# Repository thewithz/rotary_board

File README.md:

# rotary_board
A custom 65% keyboard design featuring 4 rotary encoders in place of the pg up, pg down, home, and end keys

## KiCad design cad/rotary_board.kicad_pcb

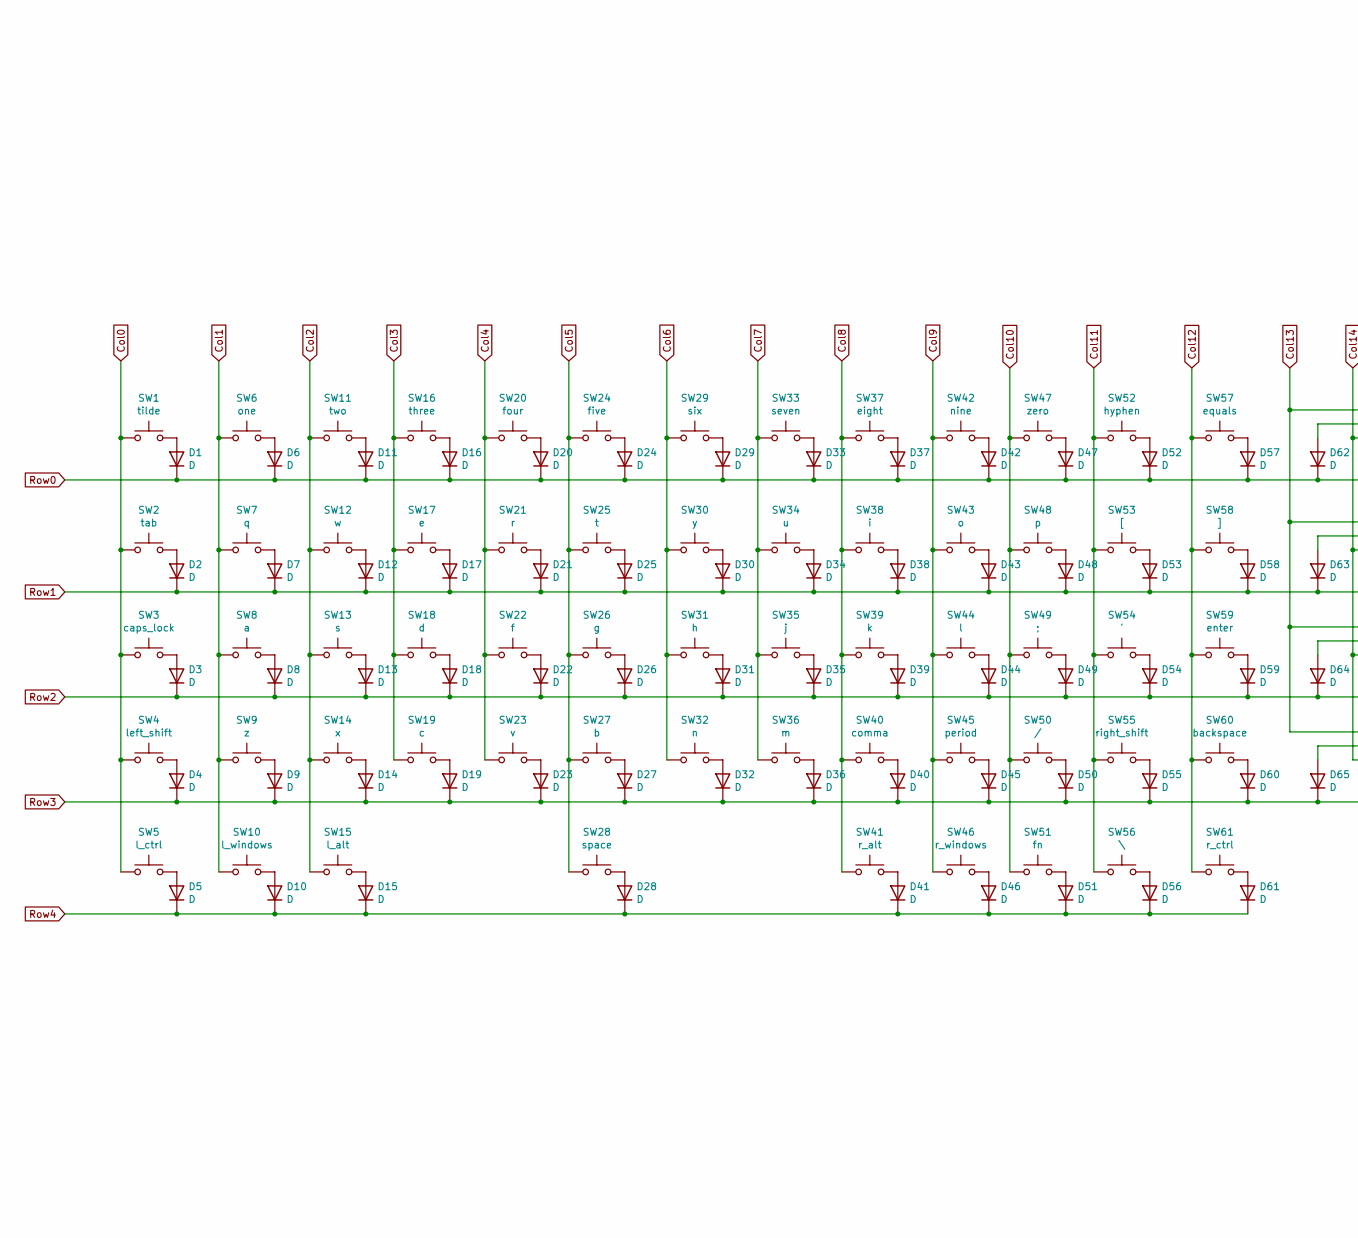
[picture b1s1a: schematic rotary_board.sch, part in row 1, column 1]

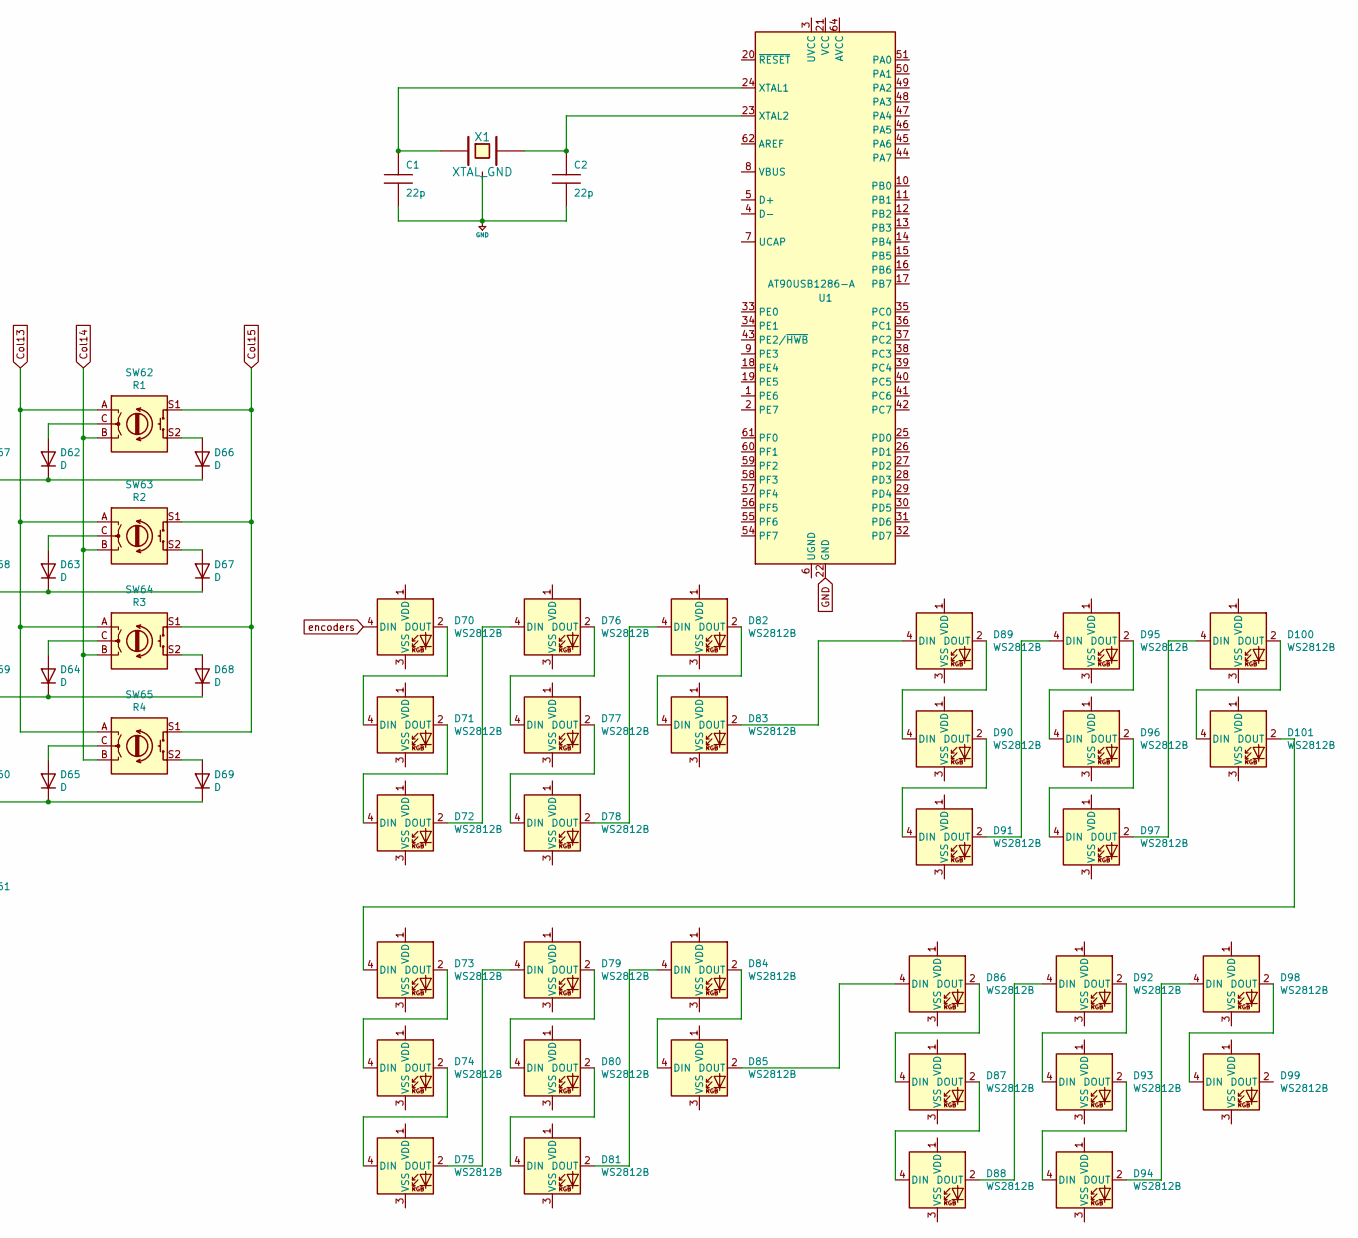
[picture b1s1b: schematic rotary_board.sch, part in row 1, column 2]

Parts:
C1, C2: 22p; CP_Elec_3x5.3
D1, D2, D3, D4, D5, D6, D7, D8, D9, D10, D11, D12, D13, D14, D15, D16, D17, D18, D19, D20, D21, D22, D23, D24, D25, D26, D27, D28, D29, D30, D31, D32, D33, D34, D35, D36, D37, D38, D39, D40, D41, D42, D43, D44, D45, D46, D47, D48, D49, D50, D51, D52, D53, D54, D55, D56, D57, D58, D59, D60, D61, D62, D63, D64, D65, D66, D67, D68, D69: D; D_SOD-123
D70, D71, D72, D73, D74, D75, D76, D77, D78, D79, D80, D81, D82, D83, D84, D85, D86, D87, D88, D89, D90, D91, D92, D93, D94, D95, D96, D97, D98, D99, D100, D101: WS2812B; LED_WS2812B_PLCC4_5.0x5.0mm_P3.2mm
SW1: tilde; SW_Cherry_MX_1.00u_PCB
SW2: tab; SW_Cherry_MX_1.50u_PCB
SW3: caps_lock; SW_Cherry_MX_1.75u_PCB
SW4: left_shift; SW_Cherry_MX_2.25u_PCB
SW5: l_ctrl; SW_Cherry_MX_1.25u_PCB
SW6: one; SW_Cherry_MX_1.00u_PCB
SW7: q; SW_Cherry_MX_1.00u_PCB
SW8: a; SW_Cherry_MX_1.00u_PCB
SW9: z; SW_Cherry_MX_1.00u_PCB
SW10: l_windows; SW_Cherry_MX_1.25u_PCB
SW11: two; SW_Cherry_MX_1.00u_PCB
SW12: w; SW_Cherry_MX_1.00u_PCB
SW13: s; SW_Cherry_MX_1.00u_PCB
SW14: x; SW_Cherry_MX_1.00u_PCB
SW15: l_alt; SW_Cherry_MX_1.25u_PCB
SW16: three; SW_Cherry_MX_1.00u_PCB
SW17: e; SW_Cherry_MX_1.00u_PCB
SW18: d; SW_Cherry_MX_1.00u_PCB
SW19: c; SW_Cherry_MX_1.00u_PCB
SW20: four; SW_Cherry_MX_1.00u_PCB
SW21: r; SW_Cherry_MX_1.00u_PCB
SW22: f; SW_Cherry_MX_1.00u_PCB
SW23: v; SW_Cherry_MX_1.00u_PCB
SW24: five; SW_Cherry_MX_1.00u_PCB
SW25: t; SW_Cherry_MX_1.00u_PCB
SW26: g; SW_Cherry_MX_1.00u_PCB
SW27: b; SW_Cherry_MX_1.00u_PCB
SW28: space; SW_Cherry_MX_6.25u_PCB
SW29: six; SW_Cherry_MX_1.00u_PCB
SW30: y; SW_Cherry_MX_1.00u_PCB
SW31: h; SW_Cherry_MX_1.00u_PCB
SW32: n; SW_Cherry_MX_1.00u_PCB
SW33: seven; SW_Cherry_MX_1.00u_PCB
SW34: u; SW_Cherry_MX_1.00u_PCB
SW35: j; SW_Cherry_MX_1.00u_PCB
SW36: m; SW_Cherry_MX_1.00u_PCB
SW37: eight; SW_Cherry_MX_1.00u_PCB
SW38: i; SW_Cherry_MX_1.00u_PCB
SW39: k; SW_Cherry_MX_1.00u_PCB
SW40: comma; SW_Cherry_MX_1.00u_PCB
SW41: r_alt; SW_Cherry_MX_1.25u_PCB
SW42: nine; SW_Cherry_MX_1.00u_PCB
SW43: o; SW_Cherry_MX_1.00u_PCB
SW44: l; SW_Cherry_MX_1.00u_PCB
SW45: period; SW_Cherry_MX_1.00u_PCB
SW46: r_windows; SW_Cherry_MX_1.25u_PCB
SW47: zero; SW_Cherry_MX_1.00u_PCB
SW48: p; SW_Cherry_MX_1.00u_PCB
SW49: ;; SW_Cherry_MX_1.00u_PCB
SW50: /; SW_Cherry_MX_1.00u_PCB
SW51: fn; SW_Cherry_MX_1.25u_PCB
SW52: hyphen; SW_Cherry_MX_1.00u_PCB
SW53: [; SW_Cherry_MX_1.00u_PCB
SW54: '; SW_Cherry_MX_1.00u_PCB
SW55: right_shift; SW_Cherry_MX_2.75u_PCB
SW56: \\; SW_Cherry_MX_1.50u_PCB
SW57: equals; SW_Cherry_MX_1.00u_PCB
SW58: ]; SW_Cherry_MX_1.00u_PCB
SW59: enter; SW_Cherry_MX_2.25u_PCB
SW60: backspace; SW_Cherry_MX_2.00u_PCB
SW61: r_ctrl; SW_Cherry_MX_1.25u_PCB
SW62: R1; RotaryEncoder_Alps_EC11E-Switch_Vertical_H20mm
SW63: R2; RotaryEncoder_Alps_EC11E-Switch_Vertical_H20mm
SW64: R3; RotaryEncoder_Alps_EC11E-Switch_Vertical_H20mm
SW65: R4; RotaryEncoder_Alps_EC11E-Switch_Vertical_H20mm
U1: AT90USB1286-A; TQFP-64_14x14mm_P0.8mm
X1: XTAL_GND; Crystal_AT310_D3.0mm_L10.0mm_Horizontal

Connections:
+5V: C1.2, C2.2, X1.3
Col0: SW1.1, SW2.1, SW3.1, SW4.1, SW5.1
Col1: SW6.1, SW7.1, SW8.1, SW9.1, SW10.1
Col2: SW11.1, SW12.1, SW13.1, SW14.1, SW15.1
Col3: SW16.1, SW17.1, SW18.1, SW19.1
Col4: SW20.1, SW21.1, SW22.1, SW23.1
Col5: SW24.1, SW25.1, SW26.1, SW27.1, SW28.1
Col6: SW29.1, SW30.1, SW31.1, SW32.1
Col7: SW33.1, SW34.1, SW35.1, SW36.1
Col8: SW37.1, SW38.1, SW39.1, SW40.1, SW41.1
Col9: SW42.1, SW43.1, SW44.1, SW45.1, SW46.1
Col10: SW47.1, SW48.1, SW49.1, SW50.1, SW51.1
Col11: SW52.1, SW53.1, SW54.1, SW55.1, SW56.1
Col12: SW57.1, SW58.1, SW59.1, SW60.1, SW61.1
Col13: SW62.A, SW63.A, SW64.A, SW65.A
Col14: SW62.B, SW63.B, SW64.B, SW65.B
Col15: SW62.S1, SW63.S1, SW64.S1, SW65.S1
GND: U1.22 (GND), U1.53 (GND), U1.63 (GND)
unnamed: C1.1, U1.24 (XTAL1), X1.1
unnamed: C2.1, U1.23 (XTAL2), X1.2
unnamed: D1.2 (A), SW1.2
unnamed: D2.2 (A), SW2.2
unnamed: D3.2 (A), SW3.2
unnamed: D4.2 (A), SW4.2
unnamed: D5.2 (A), SW5.2
unnamed: D6.2 (A), SW6.2
unnamed: D7.2 (A), SW7.2
unnamed: D8.2 (A), SW8.2
unnamed: D9.2 (A), SW9.2
unnamed: D10.2 (A), SW10.2
unnamed: D11.2 (A), SW11.2
unnamed: D12.2 (A), SW12.2
unnamed: D13.2 (A), SW13.2
unnamed: D14.2 (A), SW14.2
unnamed: D15.2 (A), SW15.2
unnamed: D16.2 (A), SW16.2
unnamed: D17.2 (A), SW17.2
unnamed: D18.2 (A), SW18.2
unnamed: D19.2 (A), SW19.2
unnamed: D20.2 (A), SW20.2
unnamed: D21.2 (A), SW21.2
unnamed: D22.2 (A), SW22.2
unnamed: D23.2 (A), SW23.2
unnamed: D24.2 (A), SW24.2
unnamed: D25.2 (A), SW25.2
unnamed: D26.2 (A), SW26.2
unnamed: D27.2 (A), SW27.2
unnamed: D28.2 (A), SW28.2
unnamed: D29.2 (A), SW29.2
unnamed: D30.2 (A), SW30.2
unnamed: D31.2 (A), SW31.2
unnamed: D32.2 (A), SW32.2
unnamed: D33.2 (A), SW33.2
unnamed: D34.2 (A), SW34.2
unnamed: D35.2 (A), SW35.2
unnamed: D36.2 (A), SW36.2
unnamed: D37.2 (A), SW37.2
unnamed: D38.2 (A), SW38.2
unnamed: D39.2 (A), SW39.2
unnamed: D40.2 (A), SW40.2
unnamed: D41.2 (A), SW41.2
unnamed: D42.2 (A), SW42.2
unnamed: D43.2 (A), SW43.2
unnamed: D44.2 (A), SW44.2
unnamed: D45.2 (A), SW45.2
unnamed: D46.2 (A), SW46.2
unnamed: D47.2 (A), SW47.2
unnamed: D48.2 (A), SW48.2
unnamed: D49.2 (A), SW49.2
unnamed: D50.2 (A), SW50.2
unnamed: D51.2 (A), SW51.2
unnamed: D52.2 (A), SW52.2
unnamed: D53.2 (A), SW53.2
unnamed: D54.2 (A), SW54.2
unnamed: D55.2 (A), SW55.2
unnamed: D56.2 (A), SW56.2
unnamed: D57.2 (A), SW57.2
unnamed: D58.2 (A), SW58.2
unnamed: D59.2 (A), SW59.2
unnamed: D60.2 (A), SW60.2
unnamed: D61.2 (A), SW61.2
unnamed: D62.2 (A), SW62.C
unnamed: D63.2 (A), SW63.C
unnamed: D64.2 (A), SW64.C
unnamed: D65.2 (A), SW65.C
unnamed: D66.2 (A), SW62.S2
unnamed: D67.2 (A), SW63.S2
unnamed: D68.2 (A), SW64.S2
unnamed: D69.2 (A), SW65.S2
unnamed: D70.2 (DOUT), D71.4 (DIN)
unnamed: D71.2 (DOUT), D72.4 (DIN)
unnamed: D72.2 (DOUT), D76.4 (DIN)
unnamed: D73.2 (DOUT), D74.4 (DIN)
unnamed: D74.2 (DOUT), D75.4 (DIN)
unnamed: D75.2 (DOUT), D79.4 (DIN)
unnamed: D76.2 (DOUT), D77.4 (DIN)
unnamed: D77.2 (DOUT), D78.4 (DIN)
unnamed: D78.2 (DOUT), D82.4 (DIN)
unnamed: D79.2 (DOUT), D80.4 (DIN)
unnamed: D80.2 (DOUT), D81.4 (DIN)
unnamed: D81.2 (DOUT), D84.4 (DIN)
unnamed: D82.2 (DOUT), D83.4 (DIN)
unnamed: D83.2 (DOUT), D89.4 (DIN)
unnamed: D84.2 (DOUT), D85.4 (DIN)
unnamed: D85.2 (DOUT), D86.4 (DIN)
unnamed: D86.2 (DOUT), D87.4 (DIN)
unnamed: D87.2 (DOUT), D88.4 (DIN)
unnamed: D88.2 (DOUT), D92.4 (DIN)
unnamed: D89.2 (DOUT), D90.4 (DIN)
unnamed: D90.2 (DOUT), D91.4 (DIN)
unnamed: D91.2 (DOUT), D95.4 (DIN)
unnamed: D92.2 (DOUT), D93.4 (DIN)
unnamed: D93.2 (DOUT), D94.4 (DIN)
unnamed: D94.2 (DOUT), D98.4 (DIN)
unnamed: D95.2 (DOUT), D96.4 (DIN)
unnamed: D96.2 (DOUT), D97.4 (DIN)
unnamed: D98.2 (DOUT), D99.4 (DIN)
unnamed: D100.2 (DOUT), D101.4 (DIN)
unnamed: D97.2 (DOUT), D100.4 (DIN)
unnamed: D73.4 (DIN), D101.2 (DOUT)
unnamed: U1.21 (VCC), U1.52 (VCC)
Row0: D1.1 (K), D6.1 (K), D11.1 (K), D16.1 (K), D20.1 (K), D24.1 (K), D29.1 (K), D33.1 (K), D37.1 (K), D42.1 (K), D47.1 (K), D52.1 (K), D57.1 (K), D62.1 (K), D66.1 (K)
Row1: D2.1 (K), D7.1 (K), D12.1 (K), D17.1 (K), D21.1 (K), D25.1 (K), D30.1 (K), D34.1 (K), D38.1 (K), D43.1 (K), D48.1 (K), D53.1 (K), D58.1 (K), D63.1 (K), D67.1 (K)
Row2: D3.1 (K), D8.1 (K), D13.1 (K), D18.1 (K), D22.1 (K), D26.1 (K), D31.1 (K), D35.1 (K), D39.1 (K), D44.1 (K), D49.1 (K), D54.1 (K), D59.1 (K), D64.1 (K), D68.1 (K)
Row3: D4.1 (K), D9.1 (K), D14.1 (K), D19.1 (K), D23.1 (K), D27.1 (K), D32.1 (K), D36.1 (K), D40.1 (K), D45.1 (K), D50.1 (K), D55.1 (K), D60.1 (K), D65.1 (K), D69.1 (K)
Row4: D5.1 (K), D10.1 (K), D15.1 (K), D28.1 (K), D41.1 (K), D46.1 (K), D51.1 (K), D56.1 (K), D61.1 (K)
encoders: D70.4 (DIN)

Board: 2 copper layers, 170 parts (69 on the bottom side), 126 nets, no tracks yet.

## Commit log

2020-10-24 first editions of plate design
2020-10-26 Uploads first try at render
2021-09-06 add files
